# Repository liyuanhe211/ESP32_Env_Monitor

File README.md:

# ESP32 Environment Monitor
A `ESP32` Micropython script with 5 temperature/humidity sensors, a CO2 sensor, and a VOC sensor. The main use case is for animal enclosure for something like turtles, geckos, or other reptiles.

## Features
<p align="center"></img></p>

 - Display 5 temperatures and humidities from 5 `AHT10` probes. (Results rounded to 0.1 °C and 1% RH.)
 - Draw a graphical representation of the temperatures with bars.
 - Connects a button to record the time since an event. (The time keeping is kept if power to the `ESP32` is lost, and will be resumed on the next power-up. So basically no RTC is needed, unless prolonged power outage is a problem.)
 - Flash-screen warning if temperature is out of range.

## Electrical connections
The components are soldered to a prototyping board, illustrated below. The left part is an independent circuit for blinking LEDs with NE555P. The connection of this part to the ESP32 is only the 5V power lines. 
<p align="center"></img></p>

# A standard thermometer and humidity monitor with screen
# Connection for ESP32

# Connect a [Parallel to I2C Chip] to a LCD2004 screen
# Just solder all pins sequentially to the screen, Direction: (pin towards [GND, VCC, SDA, SCL] pin connects to the VSS pin of the Screen

Connect [Parallel to I2C Chip] to ESP8266
GND - GND
VCC - VIN
SCL - 26
SDA - 27
Also
SDA - 10K resister - GND
SCL - 10K resister - GND

Connect Five AHT10 chip to ESP32, without pull-up resister, using internal pull up resister
Sensor-i2c A: SCL 19 SDA 22
Sensor-i2c A: SCL 18 SDA 23
Sensor-i2c A: SCL 16 SDA 17
Sensor-i2c A: SCL 2 SDA 4
Sensor-i2c A: SCL 32 SDA 33

Attach any SCD40 to any one of the AHT10 I2C channel (G-G, V-V, SCL-SCL, SDA-SDA)

Connect a Fed Pushbutton between 35 and 3V3, pull down 35 with 2k resister
Connect a Water Pushbutton between 13 and 3V3, pull down 13 with 2k resister

 - `[5V]  - [LCD2004-VCC]`
 - `[3.3V]  - [AHT10-VCCs] - [Button_Pin1]`
 - `[GND]  - [AHT10-GNDs] - [LCD2004-GND] - [Button-Pulldown-Resister_Pin1]`
 - `[ESP32-GPIO35] - [Button_Pin2] - [Button-Pulldown-Resister_Pin2]`
 - `[Sensor-A-SCL] - [GPIO19]`
 - `[Sensor-A-SDA] - [GPIO22]`
 - `[Sensor-B-SCL] - [GPIO18]`
 - `[Sensor-B-SDA] - [GPIO23]`
 - `[Sensor-C-SCL] - [GPIO16]`
 - `[Sensor-C-SDA] - [GPIO17]`
 - `[Sensor-D-SCL] - [GPIO2]`
 - `[Sensor-D-SDA] - [GPIO4]`
 - `[Sensor-E-SCL] - [GPIO32]`
 - `[Sensor-E-SDA] - [GPIO33]`
 - `[PCF8574-SCL] - [GPIO26]`
 - `[PCF8574-SDA] - [GPIO27]`
 - `[PCF8574] ≡ [LCD2004] follow PCF8574 chip instruction`

---

Light sub panel

S9014, DC current gain = 280, 
Collector-emitter voltage = 12 V
IB = 0.1 ~ 0.16 mA
Base-Emitter satuation current  = 600~800 mA

Assuming IC = 100 mA
Gain  = 50
IB = 2 mA
VB = 3 V
RB = 1Kohm

Using RB = 300 ohm

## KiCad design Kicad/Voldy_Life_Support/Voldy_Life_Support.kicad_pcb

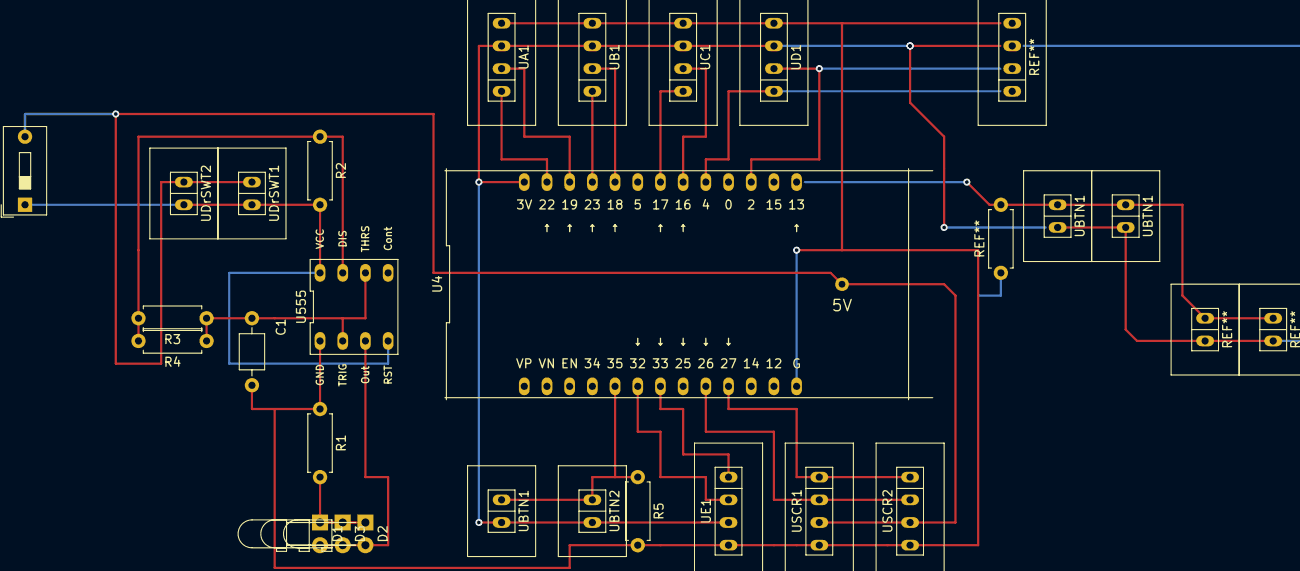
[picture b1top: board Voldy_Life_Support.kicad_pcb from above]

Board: 2 copper layers, 25 parts (0 on the bottom side), 21 nets.

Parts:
C1: 10μ; C_Axial_L3.8mm_D2.6mm_P7.50mm_Horizontal
D1, D2, D3: LED; LED_D3.0mm_Horizontal_O3.81mm_Z6.0mm
R1: 220; R_Axial_DIN0207_L6.3mm_D2.5mm_P7.62mm_Horizontal
R2: 1k; R_Axial_DIN0207_L6.3mm_D2.5mm_P7.62mm_Horizontal
R3: 220k; R_Axial_DIN0207_L6.3mm_D2.5mm_P7.62mm_Horizontal
R4: 300k; R_Axial_DIN0207_L6.3mm_D2.5mm_P7.62mm_Horizontal
R5: 2.2k; R_Axial_DIN0207_L6.3mm_D2.5mm_P7.62mm_Horizontal
SWDoor1: SW_SPST; SW_DIP_SPSTx01_Slide_9.78x4.72mm_W7.62mm_P2.54mm
U4: ESP32_Lolin
U555: NE555P
UA1: 4-Pin; SIP-4
UB1: 4-Pin; SIP-4
UBTN1, UBTN1#2, UBTN1#3, UBTN2: 2-Pin; SIP-2
UC1: 4-Pin; SIP-4
UD1: 4-Pin; SIP-4
UDrSWT1, UDrSWT2: 2-Pin; SIP-2
UE1: 4-Pin; SIP-4
USCR1, USCR2: 4-Pin; SIP-4

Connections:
+3V3: U4.3V, UA1.3, UB1.3, UBTN1#3.1, UBTN2.1, UC1.3, UD1.3, UE1.3
+5V: SWDoor1.2, U4.5V, UDrSWT1.2, UDrSWT2.2, USCR1.3, USCR2.3
GND: C1.2, R1.1, R5.2, U4.G, U555.GND, UA1.4, UB1.4, UC1.4, UD1.4, UE1.4, USCR1.4, USCR2.4
unnamed: C1.1, R3.1, R4.1, U555.THRS, U555.TRIG
unnamed: D1.1, D2.1, D3.1, R1.2
unnamed: D1.2, D2.2, D3.2, U555.Out
unnamed: R2.1, R3.2, R4.2, U555.DIS
unnamed: R2.2, SWDoor1.1, U555.RST, U555.VCC, UDrSWT1.1, UDrSWT2.1
unnamed: R5.1, U4.35, UBTN1#3.2, UBTN2.2
unnamed: U4.2, UD1.2
unnamed: U4.4, UD1.1
unnamed: U4.16, UC1.2
unnamed: U4.17, UC1.1
unnamed: U4.18, UB1.2
unnamed: U4.19, UA1.2
unnamed: U4.22, UA1.1
unnamed: U4.23, UB1.1
unnamed: U4.26, USCR1.2, USCR2.2
unnamed: U4.27, USCR1.1, USCR2.1
unnamed: U4.32, UE1.2
unnamed: U4.33, UE1.1

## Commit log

2022-10-12 Add NE555P Kicad File
2023-05-08 Add SHT20, SCD40
2023-05-13 Add datasheet
2023-07-21 Init
